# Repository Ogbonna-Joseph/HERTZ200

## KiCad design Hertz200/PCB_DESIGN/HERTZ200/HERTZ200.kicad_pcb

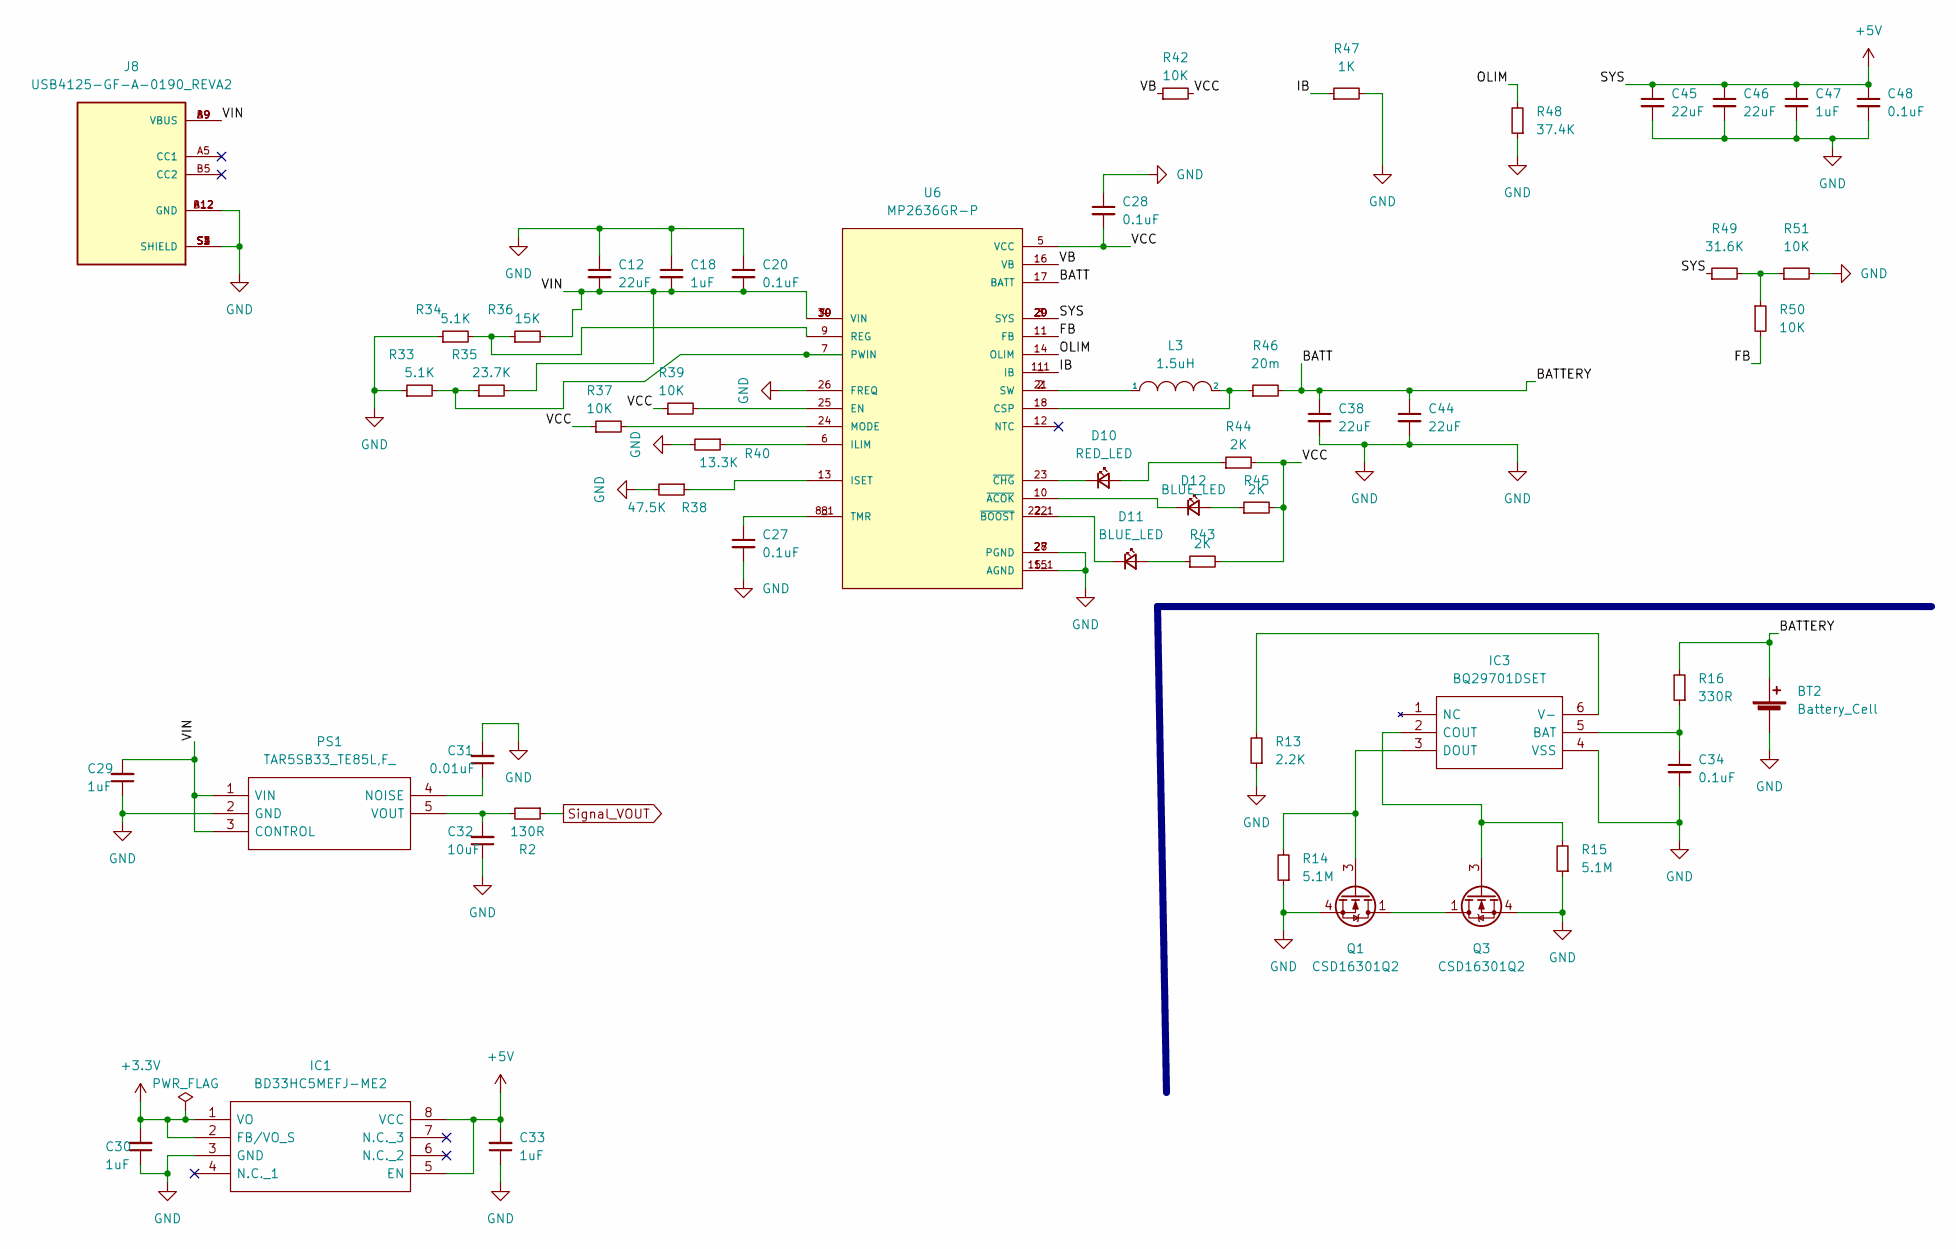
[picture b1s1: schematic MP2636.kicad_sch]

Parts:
BT2: Battery_Cell; PinHeader_1x02_P2.54mm_Vertical
C12, C38, C44, C45, C46: 22uF; C_1206_3216Metric
C18, C30, C33, C47: 1uF; C_0603_1608Metric
C20, C27, C28, C48: 0.1uF; C_0603_1608Metric
C29: 1uF; C_0805_2012Metric
C31: 0.01uF; C_0603_1608Metric
C32: 10uF; C_0603_1608Metric
C34: 0.1uF; R_0805_2012Metric
D10: RED_LED; LED_0603_1608Metric
D11, D12: BLUE_LED; LED_0603_1608Metric
IC1: BD33HC5MEFJ-ME2; SOIC127P600X100-8N; Mouser Part Number 755-BD33HC5MEFJ-ME2
IC3: BQ29701DSET; Mouser Part Number 595-BQ29701DSET
J8: USB4125-GF-A-0190_REVA2; GCT_USB4125-GF-A-0190_REVA2; PARTREV Rev A2
L3: 1.5uH; WE-HCI_7030_7040_705023
PS1: TAR5SB33_TE85L,F_; SOT95P275X140-5N; Manufacturer_Part_Number TAR5SB33(TE85L,F); Mouser Part Number 757-TAR5SB33TE85LF
Q1, Q3: CSD16301Q2; Texas_DQK
R2: 130R; R_0805_2012Metric
R13: 2.2K; R_0603_1608Metric
R14, R15: 5.1M; R_0805_2012Metric
R16: 330R; R_0805_2012Metric
R33, R34: 5.1K; R_0603_1608Metric
R35: 23.7K; R_0603_1608Metric
R36: 15K; R_0603_1608Metric
R37, R39, R42, R50, R51: 10K; R_0603_1608Metric
R38: 47.5K; R_0603_1608Metric
R40: 13.3K; R_0603_1608Metric
R43, R44, R45: 2K; R_0603_1608Metric
R46: 20m; R_2512_6332Metric
R47: 1K; R_0603_1608Metric
R48: 37.4K; R_0603_1608Metric
R49: 31.6K; R_0603_1608Metric
U6: MP2636GR-P; IC_MP2636GR-P; PARTREV 1.02

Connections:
+3V3: C30.2, IC1.1 (VO), IC1.2 (FB/VO_S); also elsewhere on the board
+5V: C33.2, C45.1, C46.1, C47.1, C48.1, IC1.5 (EN), IC1.8 (VCC), R49.1, U6.3 (SYS), U6.20 (SYS), U6.29 (SYS)
/MP2636/BATT: BT2.1 (+), C38.1, C44.1, R16.2, R46.2, U6.17 (BATT)
/MP2636/FB: R50.2, U6.11 (FB)
/MP2636/IB: R47.1, U6.1 (IB), U6.1_1 (IB)
/MP2636/OLIM: R48.2, U6.14 (OLIM)
/MP2636/VB: R42.1, U6.16 (VB)
/MP2636/VCC: C28.2, R37.1, R39.1, R42.2, R43.2, R44.2, R45.2, U6.5 (VCC)
/MP2636/VIN: C12.2, C18.2, C20.2, C29.2, J8.A9 (VBUS), J8.B9 (VBUS), PS1.1 (VIN), PS1.3 (CONTROL), R35.2, R36.2, U6.4 (VIN), U6.19 (VIN), U6.30 (VIN)
GND: BT2.2 (-), C12.1, C18.1, C20.1, C27.2, C28.1, C29.1, C30.1, C31.2, C32.1, C33.1, C34.2, C38.2, C44.2, C45.2, C46.2, C47.2, C48.2, IC1.3 (GND), IC3.4 (VSS), J8.A12 (GND), J8.B12 (GND), J8.S1 (SHIELD), J8.S2 (SHIELD), J8.S3 (SHIELD), J8.S4 (SHIELD), PS1.2 (GND), Q1.4 (S), Q1.7 (S), Q3.4 (S), Q3.7 (S), R13.1, R14.1, R15.1, R33.1, R34.1, R38.2, R40.2, R47.2, R48.1, R51.2, U6.15 (AGND), U6.15_1 (AGND), U6.26 (FREQ), U6.27 (PGND), U6.28 (PGND); also elsewhere on the board
unnamed: C27.1, U6.8 (TMR), U6.8_1 (TMR)
unnamed: C31.1, PS1.4 (NOISE)
unnamed: C32.2, PS1.5 (VOUT), R2.2
unnamed: C34.1, IC3.5 (BAT), R16.1
unnamed: D10.1 (K), U6.23 (~CHG)
unnamed: D10.2 (A), R44.1
unnamed: D11.1 (K), U6.22 (~BOOST), U6.22_1 (~BOOST)
unnamed: D11.2 (A), R43.1
unnamed 53: D12.1 (K), U6.10 (~ACOK); also elsewhere on the board
unnamed 54: D12.2 (A), R45.1; also elsewhere on the board
unnamed: IC3.2 (COUT), Q3.3 (G), R15.2
unnamed: IC3.3 (DOUT), Q1.3 (G), R14.2
unnamed: IC3.6 (V-), R13.2
unnamed: L3.1, U6.2 (SW), U6.21 (SW)
unnamed: L3.2, R46.1, U6.18 (CSP)
unnamed: Q1.1 (D), Q1.2 (D), Q1.5 (D), Q1.6 (D), Q1.8 (D), Q3.1 (D), Q3.2 (D), Q3.5 (D), Q3.6 (D), Q3.8 (D)
unnamed: R33.2, R35.1, U6.7 (PWIN)
unnamed: R34.2, R36.1, U6.9 (REG)
unnamed: R37.2, U6.24 (MODE)
unnamed: R38.1, U6.13 (ISET)
unnamed: R39.2, U6.25 (EN)
unnamed: R40.1, U6.6 (ILIM)
unnamed: R49.2, R50.1, R51.1
Signal_VOUT: R2.1; also elsewhere on the board

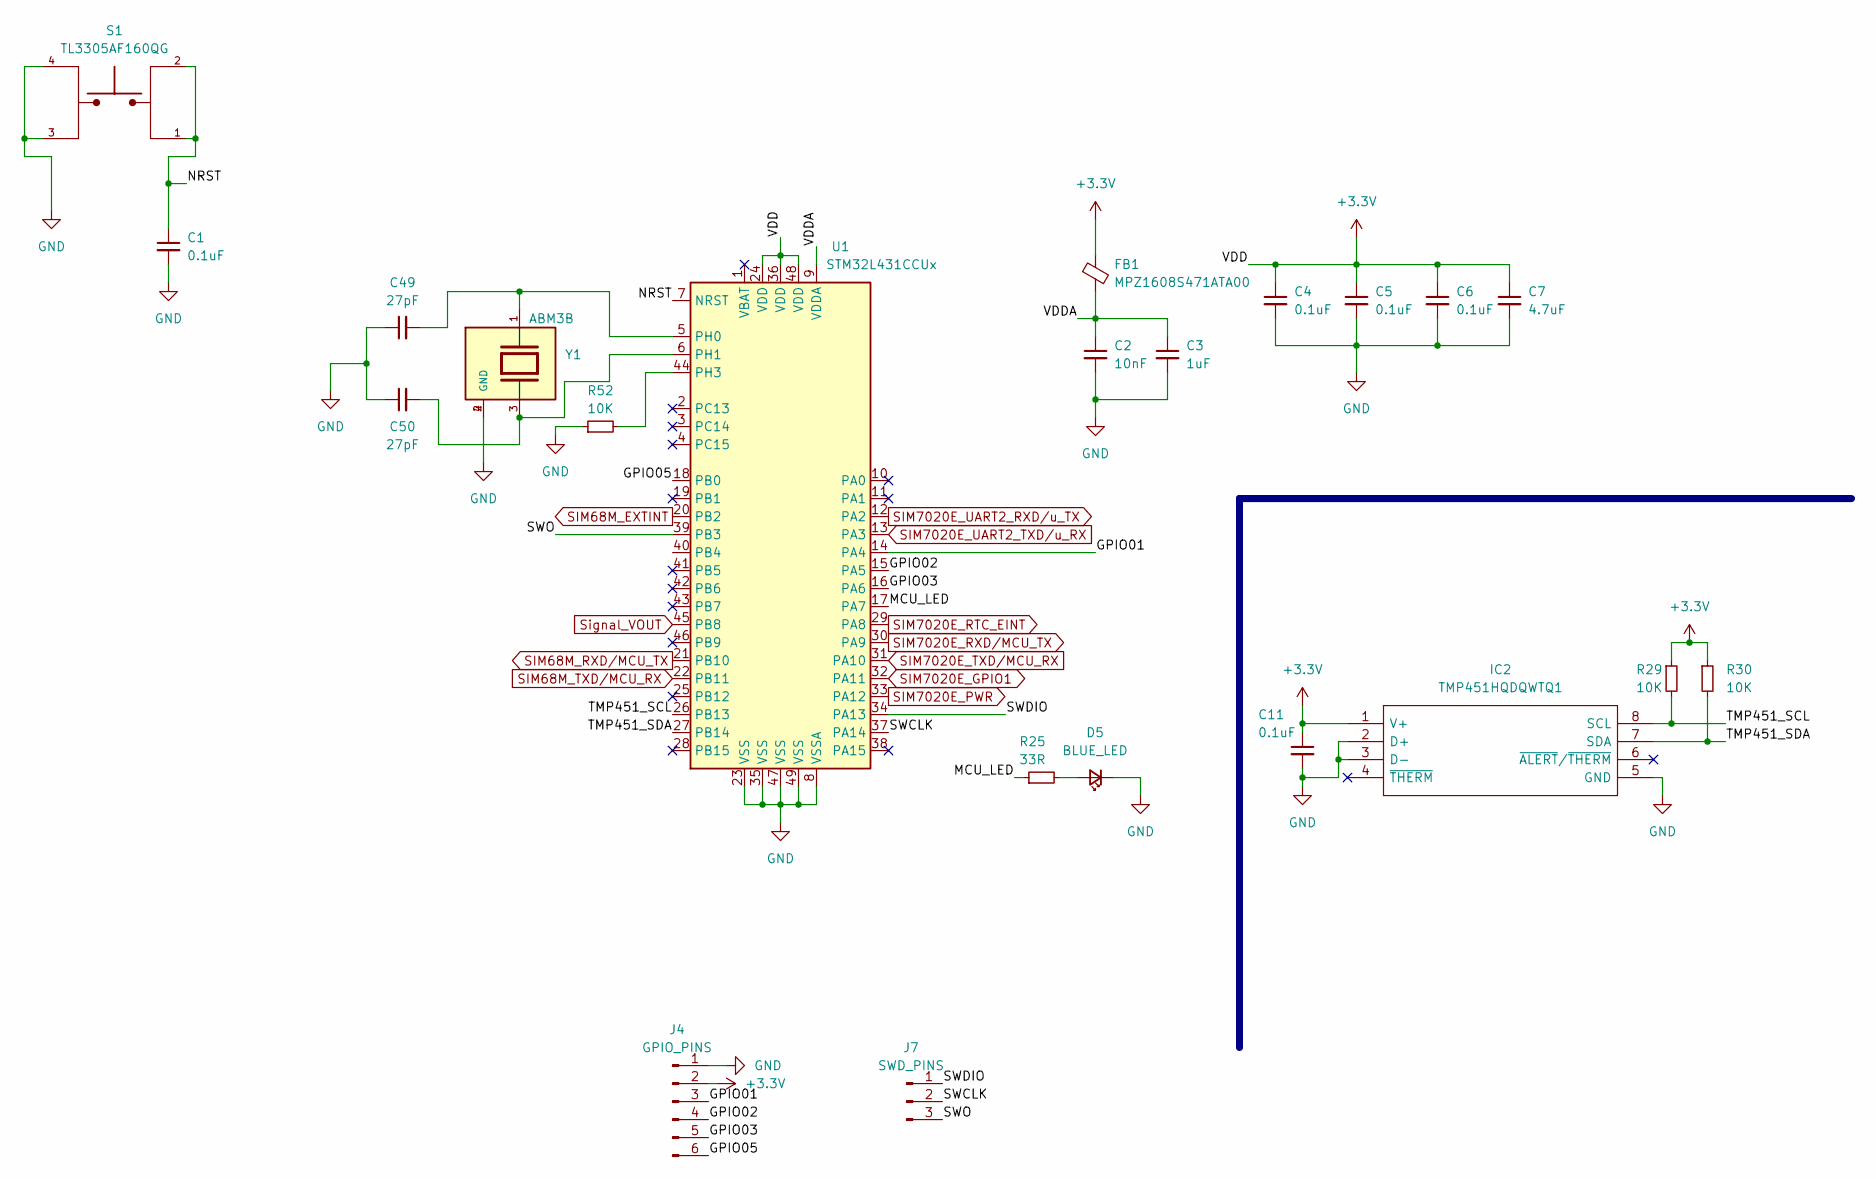
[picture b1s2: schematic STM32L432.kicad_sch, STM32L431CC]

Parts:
C1, C4, C5, C6, C11: 0.1uF; C_0603_1608Metric
C2: 10nF; C_0603_1608Metric
C3: 1uF; C_0603_1608Metric
C7: 4.7uF; C_0603_1608Metric
C49, C50: 27pF; C_0603_1608Metric
D5: BLUE_LED; LED_0805_2012Metric
FB1: MPZ1608S471ATA00; L_0603_1608Metric
IC2: TMP451HQDQWTQ1; SON50P250X200X80-8N; Mouser Part Number 595-TMP451HQDQWTQ1
J4: GPIO_PINS; PinHeader_1x06_P2.54mm_Vertical
J7: SWD_PINS; PinHeader_1x03_P2.54mm_Vertical
R25: 33R; R_0603_1608Metric
R29, R30, R52: 10K; R_0603_1608Metric
S1: TL3305AF160QG; SW_TL3305AF160QG; PARTREV C
U1: STM32L431CCUx; QFN-48-1EP_7x7mm_P0.5mm_EP5.6x5.6mm
Y1: ABM3B; XTAL_ABM3B-8.000MHZ-B2-T; PARTREV 08.25.15

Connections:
+3V3: C4.1, C5.1, C6.1, C7.1, C11.1, FB1.1, IC2.1 (V+), J4.2, R29.1, R30.1, U1.24 (VDD), U1.36 (VDD), U1.48 (VDD); also elsewhere on the board
/STM32L431_MCU/GPIO01: J4.3, U1.14 (PA4)
/STM32L431_MCU/GPIO02: J4.4, U1.15 (PA5)
/STM32L431_MCU/GPIO03: J4.5, U1.16 (PA6)
/STM32L431_MCU/GPIO05: J4.6, U1.18 (PB0)
/STM32L431_MCU/MCU_LED: R25.1, U1.17 (PA7)
/STM32L431_MCU/NRST: C1.1, S1.1, S1.2, U1.7 (NRST)
/STM32L431_MCU/SWCLK: J7.2, U1.37 (PA14)
/STM32L431_MCU/SWDIO: J7.1, U1.34 (PA13)
/STM32L431_MCU/SWO: J7.3, U1.39 (PB3)
/STM32L431_MCU/TMP451_SCL: IC2.8 (SCL), R29.2, U1.26 (PB13)
/STM32L431_MCU/TMP451_SDA: IC2.7 (SDA), R30.2, U1.27 (PB14)
/STM32L431_MCU/VDDA: C2.1, C3.1, FB1.2, U1.9 (VDDA)
GND: C1.2, C2.2, C3.2, C4.2, C5.2, C6.2, C7.2, C11.2, C49.1, C50.1, D5.1 (K), IC2.2 (D+), IC2.3 (D-), IC2.5 (GND), J4.1, R52.1, S1.3, S1.4, U1.8 (VSSA), U1.23 (VSS), U1.35 (VSS), U1.47 (VSS), U1.49 (VSS), Y1.2 (GND), Y1.4 (GND); also elsewhere on the board
unnamed: D5.2 (A), R25.2
unnamed: C49.2, U1.5 (PH0), Y1.1
unnamed: C50.2, U1.6 (PH1), Y1.3
unnamed: R52.2, U1.44 (PH3)
SIM68M_EXTINT: U1.20 (PB2); also elsewhere on the board
SIM68M_RXD/MCU_TX: U1.21 (PB10); also elsewhere on the board
SIM68M_TXD/MCU_RX: U1.22 (PB11); also elsewhere on the board
SIM7020E_GPIO1: U1.32 (PA11); also elsewhere on the board
SIM7020E_PWR: U1.33 (PA12); also elsewhere on the board
SIM7020E_RTC_EINT: U1.29 (PA8); also elsewhere on the board
SIM7020E_RXD/MCU_TX: U1.30 (PA9); also elsewhere on the board
SIM7020E_TXD/MCU_RX: U1.31 (PA10); also elsewhere on the board
SIM7020E_UART2_RXD/u_TX: U1.12 (PA2); also elsewhere on the board
SIM7020E_UART2_TXD/u_RX: U1.13 (PA3); also elsewhere on the board
Signal_VOUT: U1.45 (PB8); also elsewhere on the board

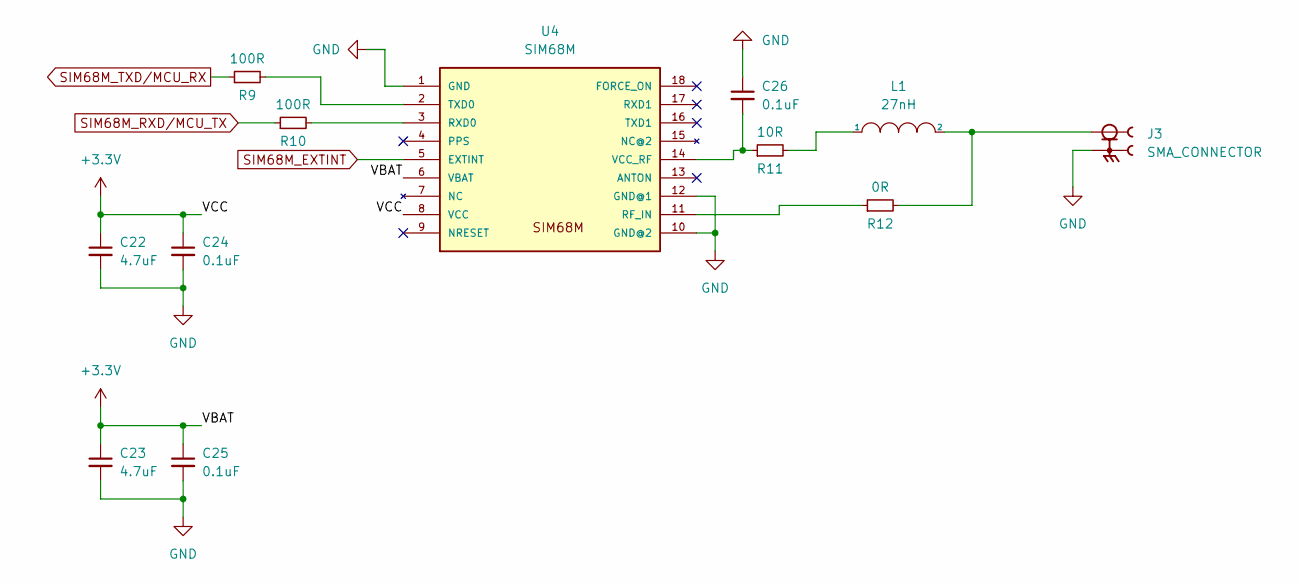
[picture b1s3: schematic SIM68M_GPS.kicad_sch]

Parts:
C22, C23: 4.7uF; C_0603_1608Metric
C24, C25, C26: 0.1uF; C_0603_1608Metric
J3: SMA_CONNECTOR; LPRS_SMA_CONNECTOR; PARTREV 1.3
L1: 27nH; L_0603_1608Metric
R9, R10: 100R; R_0603_1608Metric
R11: 10R; R_0603_1608Metric
R12: 0R; R_0603_1608Metric
U4: SIM68M

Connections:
+3V3: C22.1, C23.1, C24.1, C25.1, U4.6 (VBAT), U4.8 (VCC); also elsewhere on the board
GND: C22.2, C23.2, C24.2, C25.2, C26.1, J3.G1, J3.G2, J3.G3, J3.G4, U4.1 (GND), U4.10 (GND@2), U4.12 (GND@1); also elsewhere on the board
unnamed: C26.2, R11.1, U4.14 (VCC_RF)
unnamed: J3.1, L1.2, R12.2
unnamed: L1.1, R11.2
unnamed: R9.2, U4.2 (TXD0)
unnamed: R10.2, U4.3 (RXD0)
unnamed: R12.1, U4.11 (RF_IN)
SIM68M_EXTINT: U4.5 (EXTINT); also elsewhere on the board
SIM68M_RXD/MCU_TX: R10.1; also elsewhere on the board
SIM68M_TXD/MCU_RX: R9.1; also elsewhere on the board

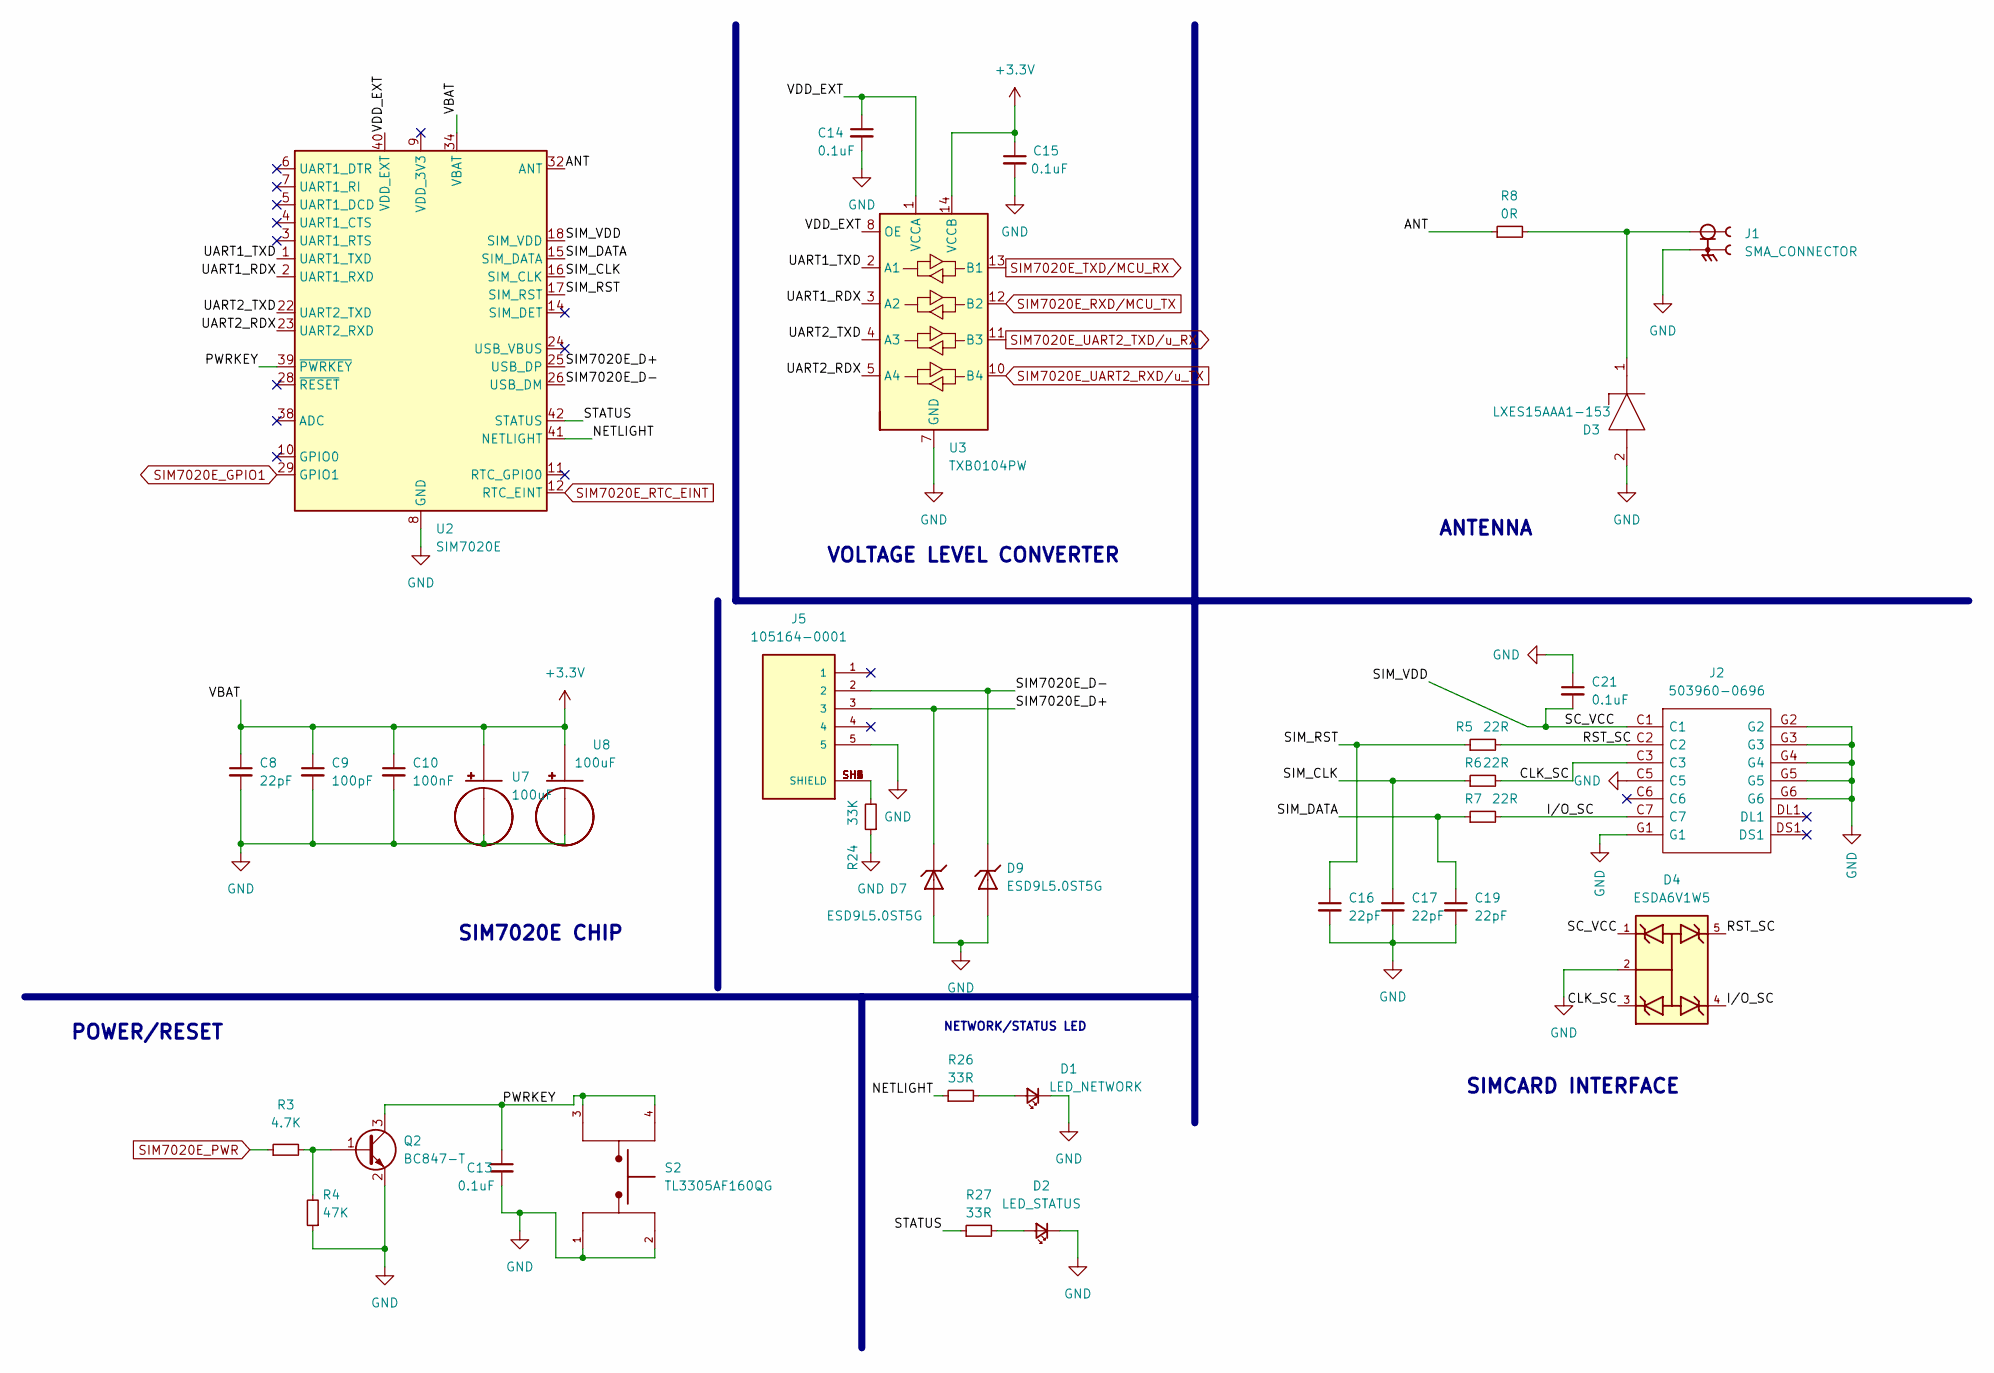
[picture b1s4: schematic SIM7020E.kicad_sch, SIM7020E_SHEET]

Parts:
C8: 22pF; C_0402_1005Metric
C9: 100pF; C_0402_1005Metric
C10: 100nF; C_0603_1608Metric
C13, C14, C15, C21: 0.1uF; C_0603_1608Metric
C16, C17, C19: 22pF; C_0603_1608Metric
D1: LED_NETWORK; LED_0805_2012Metric
D2: LED_STATUS; LED_0805_2012Metric
D3: LXES15AAA1-153; D_0402_1005Metric; Manufacturer_Part_Number ESD3V3D9-TP; Mouser Part Number 833-ESD3V3D9-TP
D4: ESDA6V1W5; SOT65P210X110-5N; PARTREV 2
D7, D9: ESD9L5.0ST5G; DIOM1006X40N; PARTREV 7
J1: SMA_CONNECTOR; LPRS_SMA_CONNECTOR; PARTREV 1.3
J2: 503960-0696; 5039600696; Manufacturer_Part_Number 503960-0696; Mouser Part Number 538-503960-0696
J5: 105164-0001; MOLEX_105164-0001; PARTREV B
Q2: BC847-T; SOT-23
R3: 4.7K; R_0603_1608Metric
R4: 47K; R_0603_1608Metric
R5, R6, R7: 22R; R_0603_1608Metric
R8: 0R; R_0603_1608Metric
R24: 33K; R_0603_1608Metric
R26, R27: 33R; R_0603_1608Metric
S2: TL3305AF160QG; SW_TL3305AF160QG; PARTREV C
U2: SIM7020E; SIMCom_SIM800C
U3: TXB0104PW; TSSOP-14_4.4x5mm_P0.65mm
U7, U8: 100uF; CAPMP7343X400N

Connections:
+3V3: C8.1, C9.1, C10.1, C15.1, U2.34 (VBAT), U2.35 (VBAT), U3.14 (VCCB), U7.+, U8.+; also elsewhere on the board
/SIM7020E/ANT: R8.1, U2.32 (ANT)
/SIM7020E/CLK_SC: D4.3, J2.C3, R6.2
/SIM7020E/I/O_SC: D4.4, J2.C7, R7.2
/SIM7020E/NETLIGHT: R26.1, U2.41 (NETLIGHT)
/SIM7020E/PWRKEY: C13.1, Q2.3 (C), S2.3, S2.4, U2.39 (~PWRKEY)
/SIM7020E/RST_SC: D4.5, J2.C2, R5.2
/SIM7020E/SC_VCC: C21.2, D4.1, J2.C1, U2.18 (SIM_VDD)
/SIM7020E/SIM7020E_D+: D7.C, J5.3, U2.25 (USB_DP)
/SIM7020E/SIM7020E_D-: D9.C, J5.2, U2.26 (USB_DM)
/SIM7020E/SIM_CLK: C17.1, R6.1, U2.16 (SIM_CLK)
/SIM7020E/SIM_DATA: C19.1, R7.1, U2.15 (SIM_DATA)
/SIM7020E/SIM_RST: C16.1, R5.1, U2.17 (SIM_RST)
/SIM7020E/STATUS: R27.1, U2.42 (STATUS)
/SIM7020E/UART1_RDX: U2.2 (UART1_RXD), U3.3 (A2)
/SIM7020E/UART1_TXD: U2.1 (UART1_TXD), U3.2 (A1)
/SIM7020E/UART2_RDX: U2.23 (UART2_RXD), U3.5 (A4)
/SIM7020E/UART2_TXD: U2.22 (UART2_TXD), U3.4 (A3)
/SIM7020E/VDD_EXT: C14.1, U2.40 (VDD_EXT), U3.1 (VCCA), U3.8 (OE)
GND: C8.2, C9.2, C10.2, C13.2, C14.2, C15.2, C16.2, C17.2, C19.2, C21.1, D1.1 (K), D2.1 (K), D3.2, D4.2, D7.A, D9.A, J1.G1, J1.G2, J1.G3, J1.G4, J2.C5, J2.G1, J2.G2, J2.G3, J2.G4, J2.G5, J2.G6, J5.5, Q2.2 (E), R4.1, R24.1, S2.1, S2.2, U2.8 (GND), U2.13 (GND), U2.19 (GND), U2.21 (GND), U2.27 (GND), U2.30 (GND), U2.31 (GND), U2.33 (GND), U2.36 (GND), U2.37 (GND), U3.7 (GND), U7.-, U8.-; also elsewhere on the board
unnamed: D1.2 (A), R26.2
unnamed: D2.2 (A), R27.2
unnamed: D3.1, J1.1, R8.2
unnamed: J5.SH1 (SHIELD), J5.SH2 (SHIELD), J5.SH3 (SHIELD), J5.SH4 (SHIELD), J5.SH5 (SHIELD), J5.SH6 (SHIELD), R24.2
unnamed: Q2.1 (B), R3.2, R4.2
SIM7020E_GPIO1: U2.29 (GPIO1); also elsewhere on the board
SIM7020E_PWR: R3.1; also elsewhere on the board
SIM7020E_RTC_EINT: U2.12 (RTC_EINT); also elsewhere on the board
SIM7020E_RXD/MCU_TX: U3.12 (B2); also elsewhere on the board
SIM7020E_TXD/MCU_RX: U3.13 (B1); also elsewhere on the board
SIM7020E_UART2_RXD/u_TX: U3.10 (B4); also elsewhere on the board
SIM7020E_UART2_TXD/u_RX: U3.11 (B3); also elsewhere on the board

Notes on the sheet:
SIMCARD INTERFACE
SIM7020E CHIP
VOLTAGE LEVEL CONVERTER
POWER/RESET
ANTENNA
NETWORK/STATUS LED

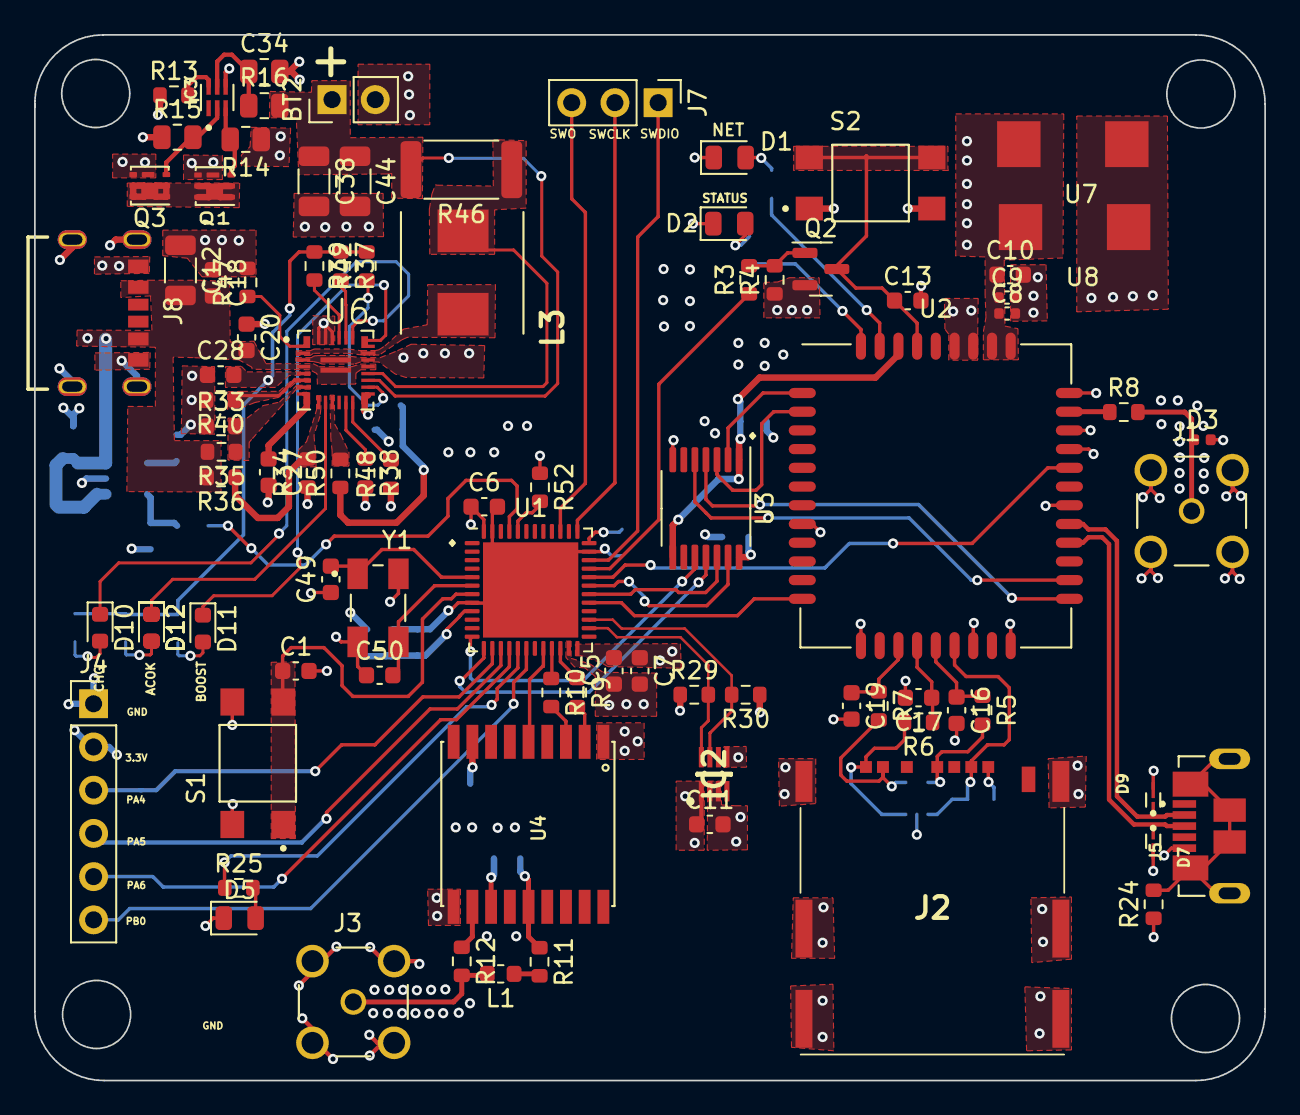
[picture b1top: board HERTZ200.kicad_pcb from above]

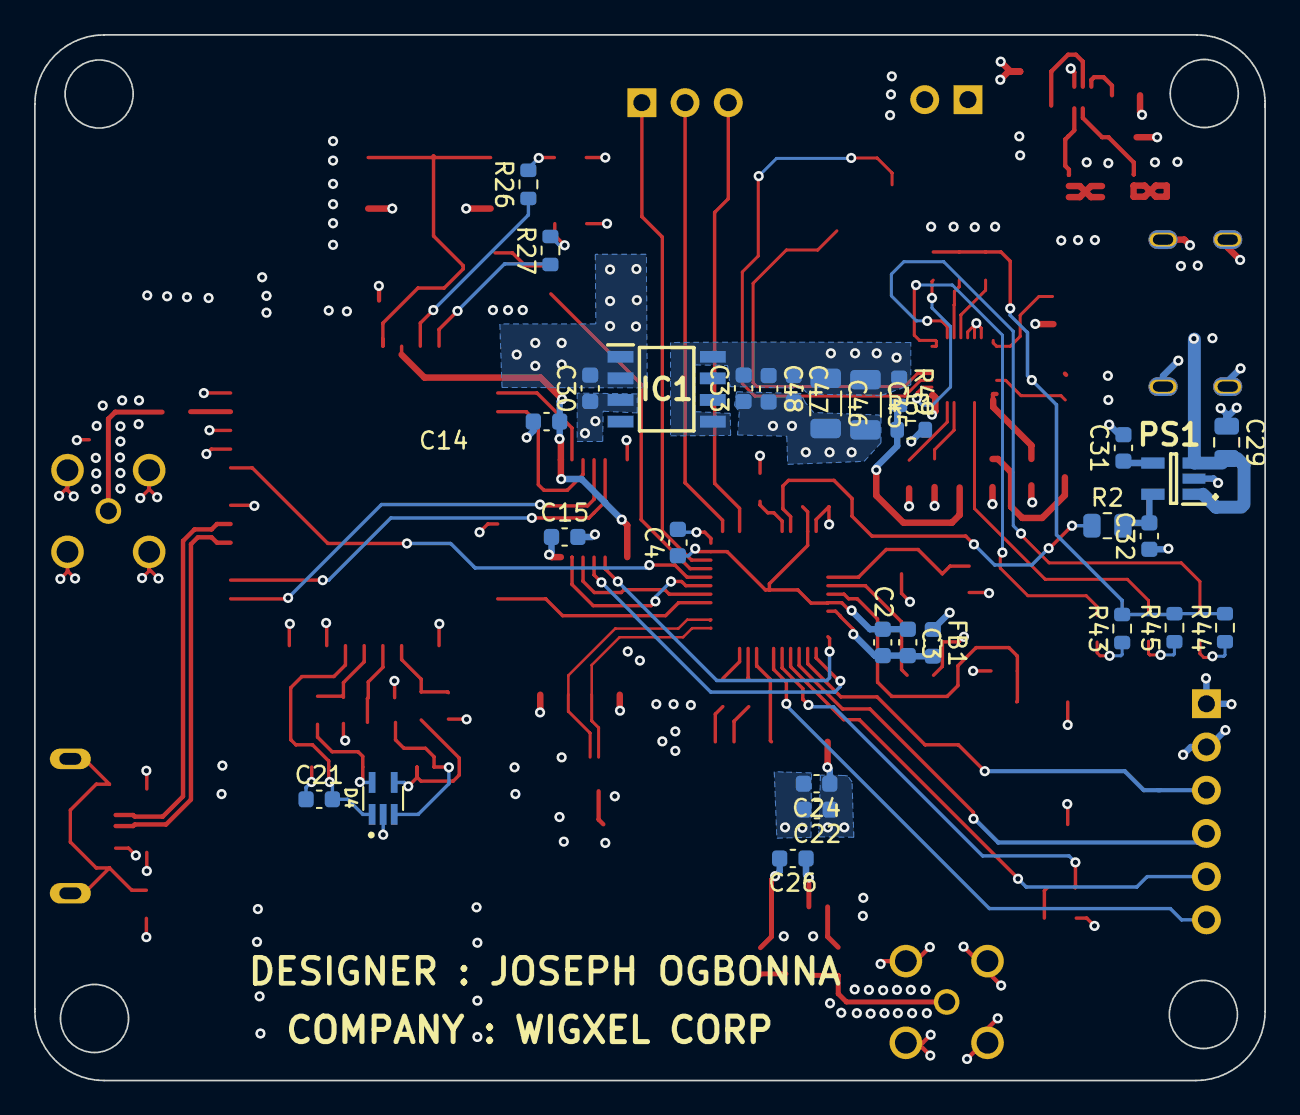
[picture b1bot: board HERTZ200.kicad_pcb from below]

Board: 4 copper layers, 72.3 x 61.5 mm, 119 parts (30 on the bottom side), 89 nets.

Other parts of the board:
D12#2: BLUE_LED; LED_0603_1608Metric

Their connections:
unnamed 53: D12#2.1 (K); also elsewhere on the board
unnamed 54: D12#2.2 (A); also elsewhere on the board

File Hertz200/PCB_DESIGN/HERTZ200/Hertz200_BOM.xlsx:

| QUANTITY | REF. DESIGNATOR | VALUE | MANF. PART NO. | MANUFACTURER | DESCRIPTION | PACKAGE | TYPE | REFERENCE | PRICE
 | 16 | C1, C4, C5, C6, C10, C11, C13, C14, C15, C20, C21, C24, C26, C27, C28, C48 | 0.1uF | 06033C104JAZ2A | Kyocera AVX | CAPACITOR | 0603 | SMT
 | 2 | C2, C31 | 10nF | C0603C103J5RACTU | KEMET | CAPACITOR | 0603 | SMT
 | 5 | C3, C18, C30, C33, C47 | 1uF | C1608X5R1H105K080AB | TDK | CAPACITOR | 0603 | SMT
 | 2 | C7, C22 | 4.7uF | GRT188R61E475KE13D | MURATA ELECTRONICS | CAPACITOR | 0603 | SMT
 | 1 | C8 | 22pF | C0402C220J5GACAUTO | KEMET | CAPACITOR | 0402 | SMT
 | 1 | C9 | 100pF | C0402C101J5GACAUTO | KEMET | CAPACITOR | 0402 | SMT
 | 5 | C12, C38, C44, C45, C46 | 22uF | CL31A226KOHNNWE | Samsung Electro-Mechanics | CAPACITOR | 1206 | SMT
 | 3 | C16, C17, C19 | 22pF | C0603C220J5GAC7867 | KEMET | CAPACITOR | 0603 | SMT
 | 1 | C29 | 1uF | GRM219R61H105KA73D | MURATA ELECTRONICS | CAPACITOR | 0805 | SMT
 | 1 | C32 | 10uF | GRM188R61E106KA73J | MURATA ELECTRONICS | CAPACITOR | 0603 | SMT
 | 1 | C34 | 0.1uF | VJ0805Y104JXXPW1BC | Vishay / Vitramon | CAPACITOR | 0805 | SMT
 | 3 | R1, R8, R12 | 0R | CR0603AJ/-000EAS | BOURNS | RESISTOR | 0603 | SMT
 | 1 | R2 | 130R | CR0805-JW-131ELF | BOURNS | RESISTOR | 0805 | SMT
 | 1 | R3 | 4.7K | SDR03EZPJ472 | ROHM SEMI CONDUCTORS | RESISTOR | 0603 | SMT
 | 1 | R4 | 47K | ERJ-3EKF4702V | PANASONIC | RESISTOR | 0603 | SMT
 | 3 | R5, R6, R7 | 22R | SFR03EZPF22R0 | ROHM SEMI CONDUCTORS | RESISTOR | 0603 | SMT
 | 2 | R9, R10 | 100R | CMP0603AFX-1000ELF | BOURNS | RESISTOR | 0603 | SMT
 | 1 | R11 | 10R | CMP0603-FX-10R0ELF | BOURNS | RESISTOR | 0603 | SMT
 | 1 | R13 | 2.2K | SDR03EZPF2201 | ROHM SEMI CONDUCTORS | RESISTOR | 0603 | SMT
 | 2 | R14, R15 | 5.1M | ESR10EZPJ515 | ROHM SEMI CONDUCTORS | RESISTOR | 0805 | SMT
 | 1 | R16 | 330R | CMP0805AFX-3300ELF | BOURNS | RESISTOR | 0805 | SMT
 | 1 | R24 | 33K | SDR03EZPJ333 | ROHM SEMI CONDUCTORS | RESISTOR | 0603 | SMT
 | 3 | R25, R26, R27 | 33R | SDR03EZPF33R0 | ROHM SEMI CONDUCTORS | RESISTOR | 0603 | SMT
 | 7 | R29, R30, R37, R39, R42, R50, R51 | 10K | CMP0603AFX-1002ELF | BOURNS | RESISTOR | 0603 | SMT
 | 2 | R33, R34 | 5.1K | SDR03EZPF5101 | ROHM SEMI CONDUCTORS | RESISTOR | 0603 | SMT
 | 1 | R35 | 23.7K | ERJ-UP3F2372V | PANASONIC | RESISTOR | 0603 | SMT
 | 1 | R36 | 15K | SDR03EZPJ153 | ROHM SEMI CONDUCTORS | RESISTOR | 0603 | SMT
 | 1 | R38 | 47.5K | ERJ-UP3F4752V | PANASONIC | RESISTOR | 0603 | SMT
 | 1 | R40 | 13.3K | ERJ-UP3F1332V | PANASONIC | RESISTOR | 0603 | SMT
 | 3 | R43, R44, R45 | 2K | SFR03EZPF2001 | ROHM SEMI CONDUCTORS | RESISTOR | 0603 | SMT
 | 1 | R46 | 20m | RL3264-6-R020-FN | CYNTEC | RESISTOR | 2512 | SMT
 | 1 | R47 | 1K | RC0603FR-071KL | YAGEO | RESISTOR | 0603 | SMT
 | 1 | R48 | 37.4K | RC0603FR-0737K4L | YAGEO | RESISTOR | 0603 | SMT
 | 1 | R49 | 31.6K | RC0603FR-0731K6L | YAGEO | RESISTOR | 0603 | SMT
 | 1 | D1 | LED_NETWORK | 150080RS75000 | Wurth Elektronik | LED | 0805 | SMT
 | 1 | D2 | LED_STATUS | 150080RS75000 | Wurth Elektronik | LED | 0805 | SMT
 | 1 | D3 | LXES15AAA1-153 | LXES15AAA1-153 | MURATA ELECTRONICS |  | 0402 | SMT
 | 1 | D4 | ESDA6V1W5 | ESDA6V1W5 | STMicroelectronics | ESD |  | SMT
 | 1 | D5 | BLUE_LED | 150060RS75000 | Wurth Elektronik | LED | 0805 | SMT
 | 1 | D6 | ESD |  |  |  | 0603 | SMT
 | 2 | D7, D9 | ESD9L5.0ST5G | ESD9L5.0ST5G | ONSEMI | ESD
 | 1 | D10 | BLUE_LED | LB Q39E-L2OO-35-1 | ams OSRAM | LED | 0603 | SMT
 | 2 | D11, D12 | BLUE_LED | LB Q39E-L2OO-35-1 | ams OSRAM | LED | 0603 | SMT
 | 1 | IC1 | BD33HC5MEFJ-ME2 | BD33HC5MEFJ-ME2 | ROHM Semiconductor | LDO REGULATOR | HTSOP-J-8 | SMT
 | 1 | IC2 | TMP451HQDQWTQ1 | TMP451HQDQWTQ1 | TEXAS INSTRUMENT | TEMPERATURE SENSOR | WSON-8 | SMT
 | 1 | IC3 | BQ29701DSET | BQ29701DSET | TEXAS INSTRUMENT | BATTERY MANAGEMENT | WSON-6 | SMT
 | 2 | J1, J3 | SMA_CONNECTOR | SMA CONNECTOR | LPRS | CONNECTOR STRAIGHT |  | PTH
 | 1 | J2 | 503960-0696 | 503960-0696 | MOLEX | SIM CARD CONNECTOR |  | SMT
 | 1 | J4 | GPIO_PINS |  |  |  |  | PTH
 | 1 | J5 | 105164-0001 | 105164-0001 | MOLEX | USB TYPE B CONNECTOR |  | SMT
 | 1 | J7 | SWD_PINS | 87220-3 | TE CONNECTIVITY | FEMALE PIN CONNECTOR |  | PTH
 | 1 | J8 | USB4125-GF-A-0190_REVA2 | USB4125-GF-A-0190 | GCT | USB TYPE C CONNECTOR |  | SMT
 | 1 | L1 | 27nH | B82496C3270J | Epcos/TDK | INDUCTOR | 0603 | SMT
 | 1 | L3 | 1.5uH | 744311150 | Wurth Elektronik | INDUCTOR |  | SMT
 | 1 | PS1 | TAR5SB33_TE85L,F_ | TAR5S33UTE85LF | TOSHIBA | LDO REGULATOR | SOT-353-5 | SMT
 | 2 | Q1, Q3 | CSD16301Q2 | CSD16301Q2 | TEXAS INSTRUMENT | MOSFET | WSON-6 | SMT
 | 1 | Q2 | BC847-T | BC847-T | RECTRON | TRASISTOR | SOT23-3 | SMT
 | 2 | S1, S2 | TL3305AF160QG | TL3305AF160QG | TEXAS INSTRUMENT | TACTILE SWITCH |  | SMT
 | 1 | U1 | STM32L431CCUx | STM32L431CCU6 | STMicroelectronics | MICROCONTROLLER | UFQFPN-48 | SMT
 | 1 | U2 | SIM7020E | SIM7020E | SIMCOM | NB-IOT MODULE | LCC, 42PIN | SMT
 | 1 | U3 | TXB0104PW | TXB0104PWR | TEXAS INSTRUMENT | VOLTAGE LEVEL TRANSLATOR | 14-TSSOP | SMT
 | 1 | U4 | SIM68M | SIM68M | SIMCOM | GPS/GNSS |  | SMT
 | 1 | U6 | MP2636GR-P | MP2636GR-P | Monolithic Power Systems (MPS) | BATTERY MANAGEMENT |  | SMT
 | 2 | U7, U8 | 100uF | T491X107K025AT | KEMET | CAPACITOR POLARIZED |  | SMT
 | 1 | BT1 |  | JST XH 2.54mm 2-Pin |  | FEMALE BATTERY CONNECTOR |  | PTH

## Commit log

2022-05-27 Power_for_Chips
2022-05-28 BQ24195_CHIP_SELECTION
2022-05-30 Starting_PCB
2022-05-30 start-pcb
2022-06-01 SIMCARD-INTERFACE-SLOTH
2022-06-01 SIMCARD-POWER-SECTION
2022-06-04 antenne
2022-06-04 Voltage_Level_Shifter
2022-06-05 Voltage_Shifter01
2022-06-10 schematics_Power_section
2022-06-14 MCU-PIN-ASSIGNMENT
2022-06-18 schamtics_finish
2022-06-25 Component_selection
2022-06-29 layout
2022-07-01 layout02
2022-08-29 TEMPERATURE SENSOR ROUTING
2022-09-07 ROUTE DONE
2022-09-10 Finished Schematics Review
2024-01-08 Mesh Electricity Design
